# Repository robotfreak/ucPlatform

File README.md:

# ucPlatform
A nodular micro controller test platform. For different micro controller boards(arduino nano, adafruit feather, wio terminal). Support libraries for different controllers (atmega, arm cortex, esp8266, esp32, rp2040) and different . Modular system with test boards for different uses (basisc io, sensors, actors)

# micro controller boards

Each board has a similar design. There is a female header connector for the controller board. 

## IOs

All IOs of the controller boards have 3pin breakout connectors (signal, vcc, gnd). Depending on the controller IO supply voltage the IO pins headers are 3.3V or 5V compatble. For external components that needs 5V on a 3.3V system or 3.3V on a 5V system there is a level shifter for 4 IOs on board  

## Power supply 

An external power supply (6..12V round connector 5.5mm outer 2.1mm inner diameter) is needed. Also an USB cable to power the controller board. The controller board will not be powered from the external power supply and vice versa, the controller board will not power any external components.

On each board is an onboard power supply to generate 5V and 3.3V for the controller and the peripheral. A standarized connector will supply add on boards with 5V, 3.3V and the output voltage of the external power supply.

## Arduino nano board

Board for classic 8bit Arduino controllers like Arduino nano, or micro. 5V compatible IOs, 3V3 support via onboard level converter. The Arduino Nano has 14 digital IOs and 8 analog inputs. Some pins with special functions like:
* UART (Rx, Tx) 
* I2C (sda, scl)
* SPI (miso, mosi, sck, en) 

## Adafruit Feather board

Board for controller boards compatible to Adafruit feather. There exists Adafruit Feather boards for most modern 32bit micro controllers that exists on the market like:
* ARM Cortex M0 or M4, 
* ESP8266 and ESP32, 
* Raspberry Pi RP2040, 
* nRF51 and nRF52  

Most boards has ports with special functions like:
* UART (rx, tx), 
* I2C (sda, scl),
* SPI (miso, mosi, sck, en)
* I2S (digital audio interface)
* DAC (digital analog converter)

## Seeed Studio Wio Terminal / Raspberry Pi board

The Seeed Studio Wio Terminal is a powerful conmtroller board with an ARM Cortex M4 controller, an extra WiFi controller, onboard TFT display, mini joystick and 2 buttons. All IOs are on a 40pins header on the buttom of the board. The pinout is compatible to the Rasperry Pi, so instead of the Wio Terminal a Raspberry Pi can be connected to this board

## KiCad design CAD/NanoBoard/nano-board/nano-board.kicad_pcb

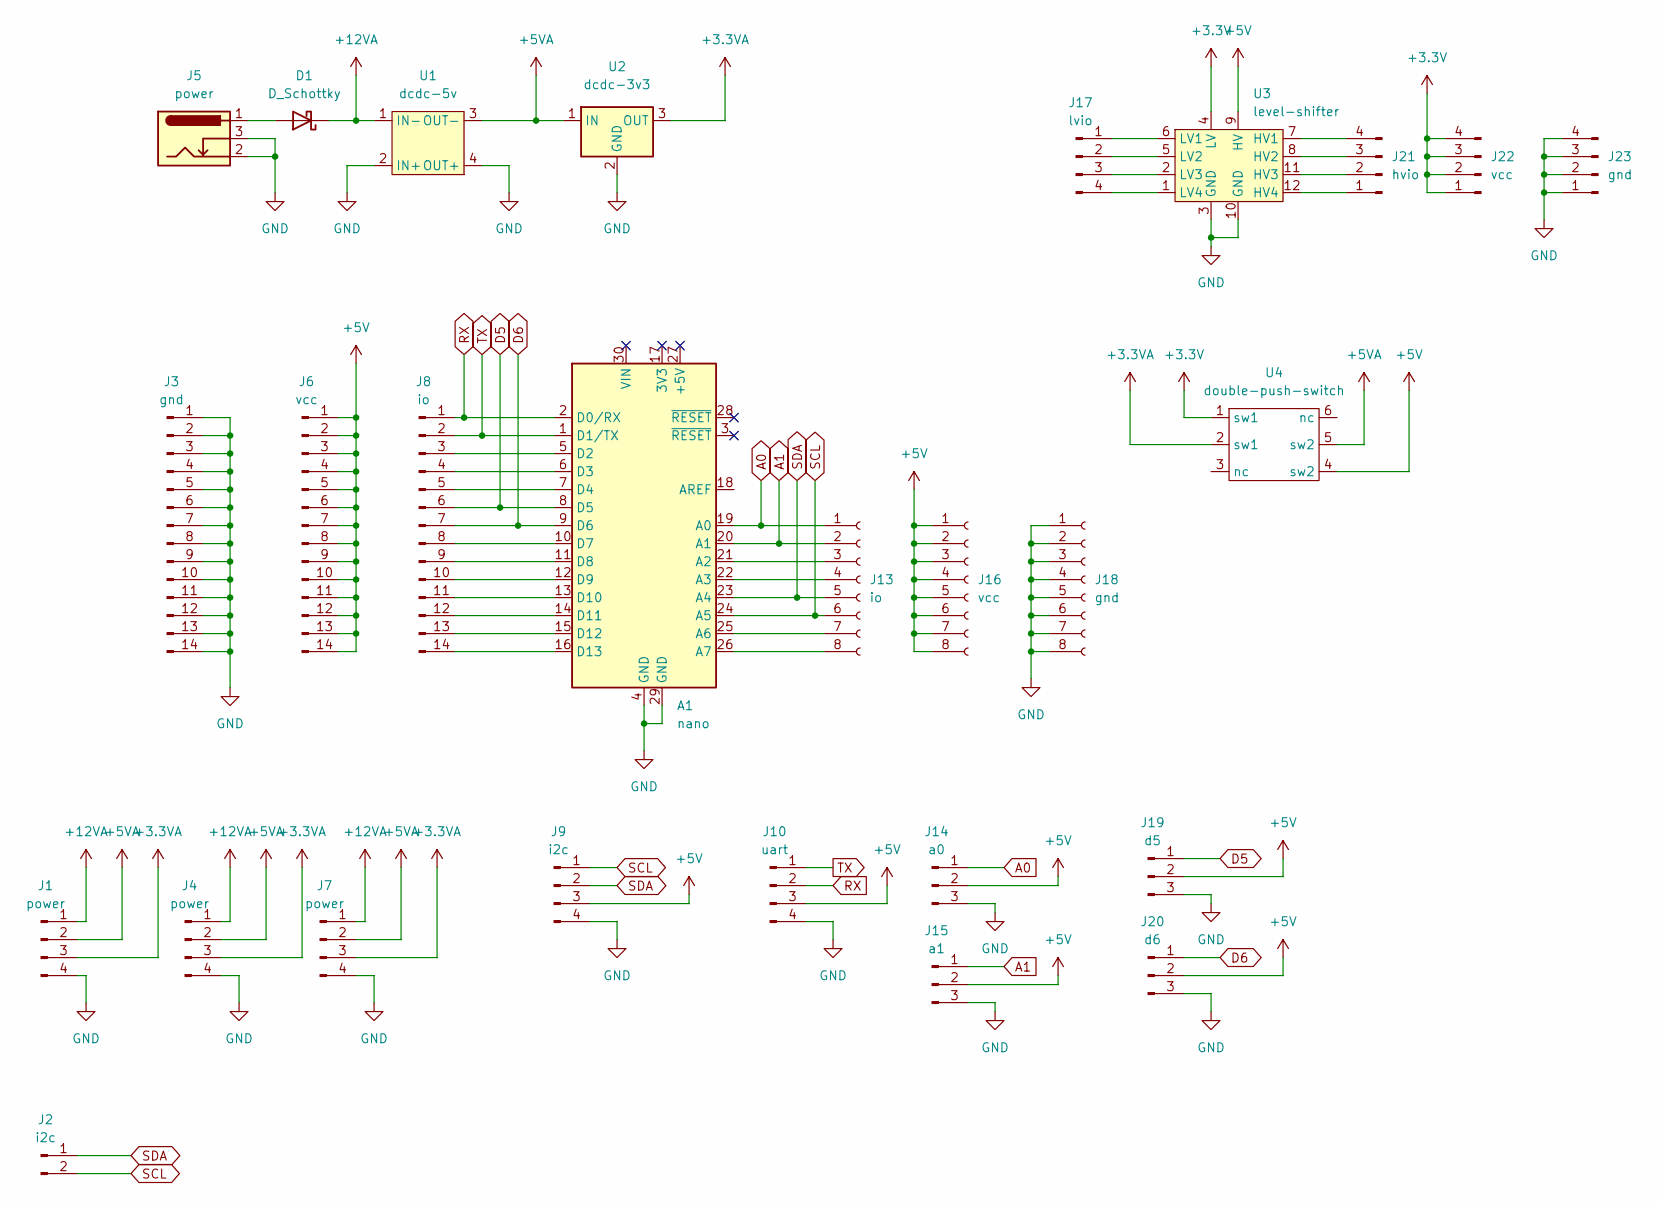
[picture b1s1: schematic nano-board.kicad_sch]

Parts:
A1: nano; Arduino_Nano
D1: D_Schottky; D_1210_3225Metric
J1, J4, J7: power; TerminalBlock_bornier-4_P5.08mm
J2: i2c; TerminalBlock_bornier-2_P5.08mm
J3: gnd; PinSocket_1x14_P2.54mm_Vertical
J5: power; BarrelJack_Horizontal
J6: vcc; PinSocket_1x14_P2.54mm_Vertical
J8: io; PinSocket_1x14_P2.54mm_Vertical
J9: i2c; PinSocket_1x04_P2.54mm_Vertical
J10: uart; PinSocket_1x04_P2.54mm_Vertical
J13: io; PinSocket_1x08_P2.54mm_Vertical
J14: a0; PinSocket_1x03_P2.54mm_Vertical
J15: a1; PinSocket_1x03_P2.54mm_Vertical
J16: vcc; PinSocket_1x08_P2.54mm_Vertical
J17: lvio; PinSocket_1x04_P2.54mm_Vertical
J18: gnd; PinSocket_1x08_P2.54mm_Vertical
J19: d5; PinSocket_1x03_P2.54mm_Vertical
J20: d6; PinSocket_1x03_P2.54mm_Vertical
J21: hvio; PinSocket_1x04_P2.54mm_Vertical
J22: vcc; PinSocket_1x04_P2.54mm_Vertical
J23: gnd; PinSocket_1x04_P2.54mm_Vertical
U1: dcdc-5v; dcdc-converter
U2: dcdc-3v3; Converter_DCDC_Murata_OKI-78SR_Vertical
U3: level-shifter; dip-12pin
U4: double-push-switch; dip-6pin

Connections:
+3.3V: J22.1, J22.2, J22.3, J22.4, U3.4 (LV), U4.1 (sw1)
+3.3VA: J1.3, J4.3, J7.3, U2.3 (OUT), U4.2 (sw1)
+5V: J6.1, J6.2, J6.3, J6.4, J6.5, J6.6, J6.7, J6.8, J6.9, J6.10, J6.11, J6.12, J6.13, J6.14, J9.3, J10.3, J14.2, J15.2, J16.1, J16.2, J16.3, J16.4, J16.5, J16.6, J16.7, J16.8, J19.2, J20.2, U3.9 (HV), U4.4 (sw2)
+5VA: J1.2, J4.2, J7.2, U1.3 (OUT-), U2.1 (IN), U4.5 (sw2)
+12VA: D1.1 (K), J1.1, J4.1, J7.1, U1.1 (IN-)
A0: A1.19 (A0), J13.1, J14.1
A1: A1.20 (A1), J13.2, J15.1
D5: A1.8 (D5), J8.6, J19.1
D6: A1.9 (D6), J8.7, J20.1
GND: A1.4 (GND), A1.29 (GND), J1.4, J3.1, J3.2, J3.3, J3.4, J3.5, J3.6, J3.7, J3.8, J3.9, J3.10, J3.11, J3.12, J3.13, J3.14, J4.4, J5.2, J5.3, J7.4, J9.4, J10.4, J14.3, J15.3, J18.1, J18.2, J18.3, J18.4, J18.5, J18.6, J18.7, J18.8, J19.3, J20.3, J23.1, J23.2, J23.3, J23.4, U1.2 (IN+), U1.4 (OUT+), U2.2 (GND), U3.3 (GND), U3.10 (GND)
unnamed: A1.5 (D2), J8.3
unnamed: A1.6 (D3), J8.4
unnamed: A1.7 (D4), J8.5
unnamed: A1.10 (D7), J8.8
unnamed: A1.11 (D8), J8.9
unnamed: A1.12 (D9), J8.10
unnamed: A1.13 (D10), J8.11
unnamed: A1.14 (D11), J8.12
unnamed: A1.15 (D12), J8.13
unnamed: A1.16 (D13), J8.14
unnamed: A1.21 (A2), J13.3
unnamed: A1.22 (A3), J13.4
unnamed: A1.25 (A6), J13.7
unnamed: A1.26 (A7), J13.8
unnamed: D1.2 (A), J5.1
unnamed: J17.1, U3.6 (LV1)
unnamed: J17.2, U3.5 (LV2)
unnamed: J17.3, U3.2 (LV3)
unnamed: J17.4, U3.1 (LV4)
unnamed: J21.1, U3.12 (HV4)
unnamed: J21.2, U3.11 (HV3)
unnamed: J21.3, U3.8 (HV2)
unnamed: J21.4, U3.7 (HV1)
RX: A1.2 (D0/RX), J8.1, J10.2
SCL: A1.24 (A5), J2.2, J9.1, J13.6
SDA: A1.23 (A4), J2.1, J9.2, J13.5
TX: A1.1 (D1/TX), J8.2, J10.1

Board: 2 copper layers, 27 parts (0 on the bottom side), 37 nets, no tracks yet.

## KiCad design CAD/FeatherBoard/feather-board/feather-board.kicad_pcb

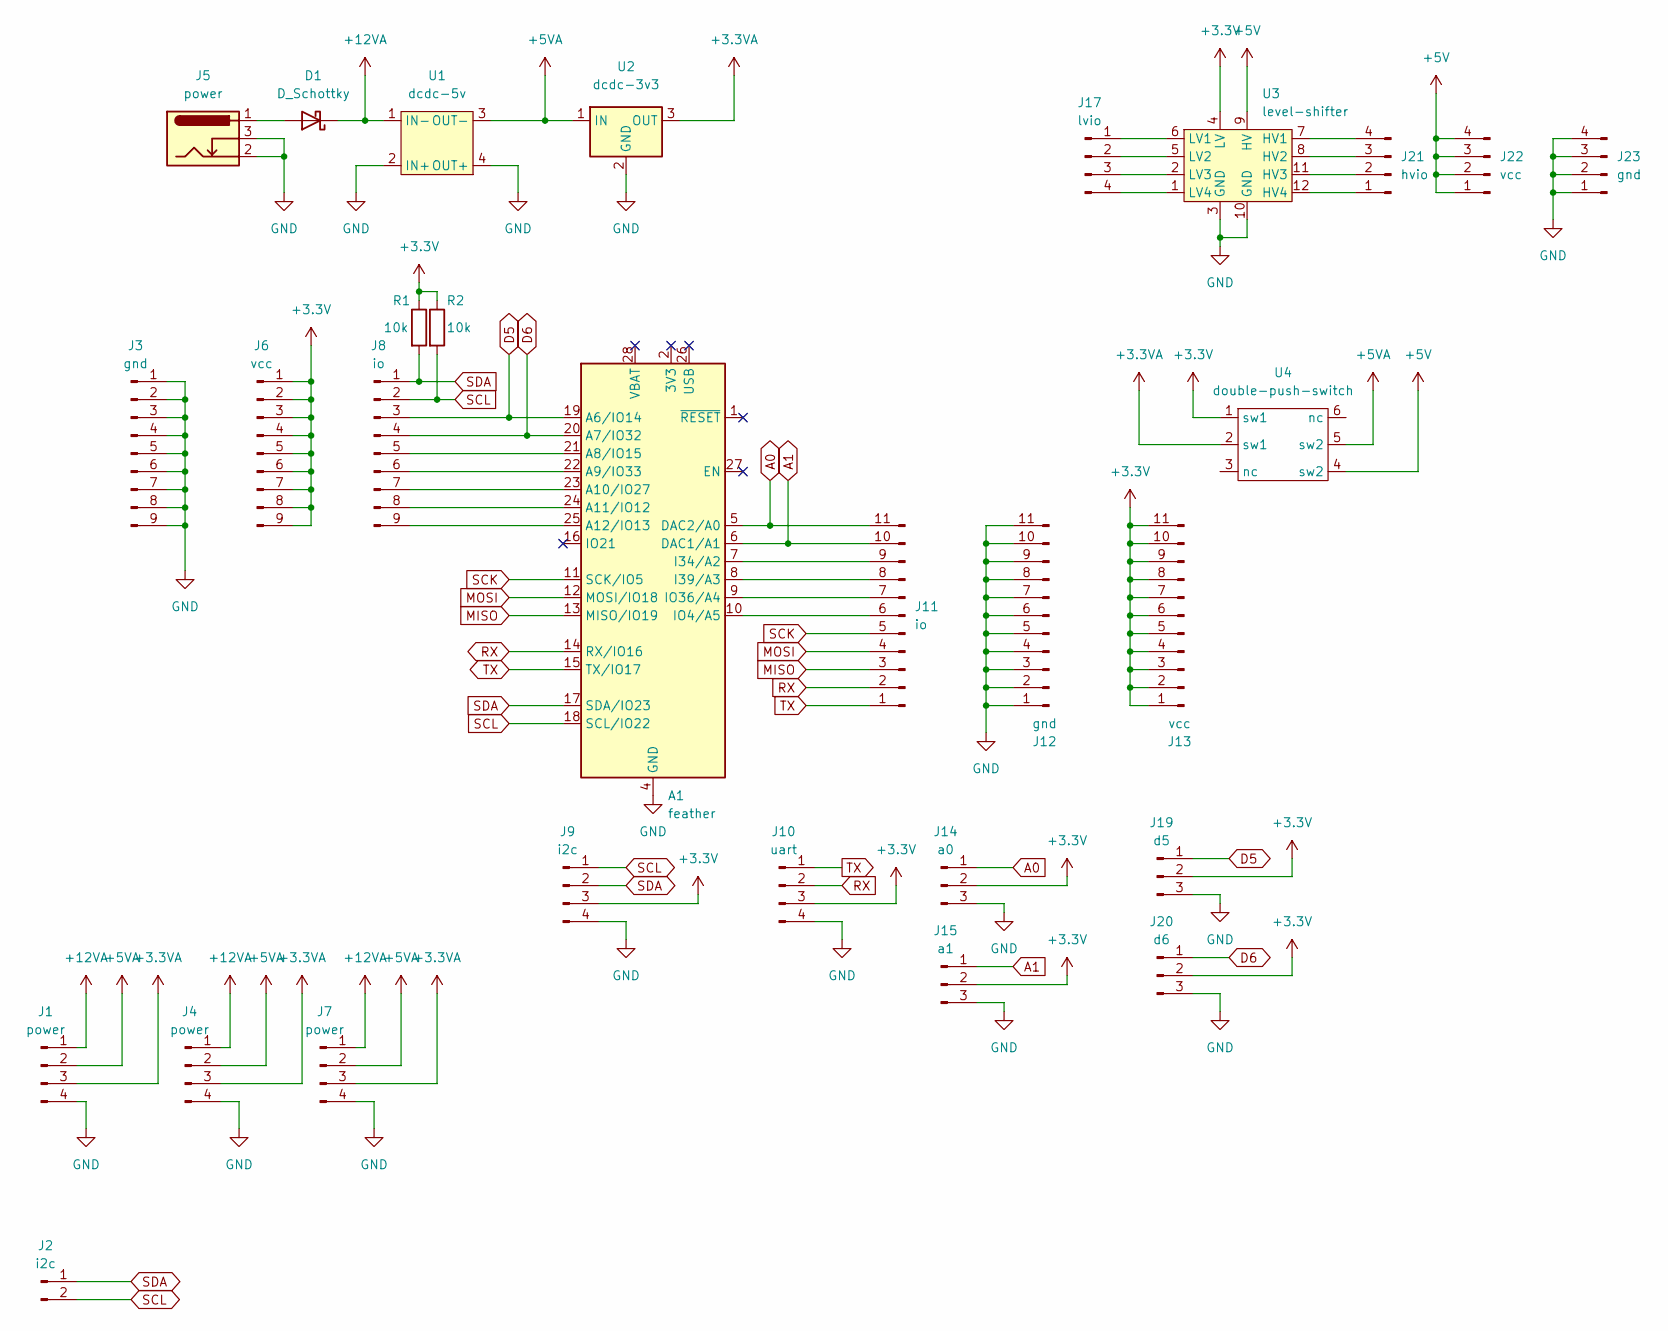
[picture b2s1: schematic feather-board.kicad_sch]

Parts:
A1: feather; Adafruit_Feather
D1: D_Schottky; D_1210_3225Metric
J1, J4, J7: power; TerminalBlock_bornier-4_P5.08mm
J2: i2c; TerminalBlock_bornier-2_P5.08mm
J3: gnd; PinHeader_1x09_P2.54mm_Vertical
J5: power; BarrelJack_Horizontal
J6: vcc; PinHeader_1x09_P2.54mm_Vertical
J8: io; PinHeader_1x09_P2.54mm_Vertical
J9: i2c; PinSocket_1x04_P2.54mm_Vertical
J10: uart; PinSocket_1x04_P2.54mm_Vertical
J11: io; PinHeader_1x11_P2.54mm_Vertical
J12: gnd; PinHeader_1x11_P2.54mm_Vertical
J13: vcc; PinHeader_1x11_P2.54mm_Vertical
J14: a0; PinSocket_1x03_P2.54mm_Vertical
J15: a1; PinSocket_1x03_P2.54mm_Vertical
J17: lvio; PinSocket_1x04_P2.54mm_Vertical
J19: d5; PinSocket_1x03_P2.54mm_Vertical
J20: d6; PinSocket_1x03_P2.54mm_Vertical
J21: hvio; PinSocket_1x04_P2.54mm_Vertical
J22: vcc; PinSocket_1x04_P2.54mm_Vertical
J23: gnd; PinSocket_1x04_P2.54mm_Vertical
R1, R2: 10k; R_1206_3216Metric
U1: dcdc-5v; dcdc-converter
U2: dcdc-3v3; Converter_DCDC_Murata_OKI-78SR_Vertical
U3: level-shifter; dip-12pin
U4: double-push-switch; dip-6pin

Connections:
+3.3V: J6.1, J6.2, J6.3, J6.4, J6.5, J6.6, J6.7, J6.8, J6.9, J9.3, J10.3, J13.1, J13.2, J13.3, J13.4, J13.5, J13.6, J13.7, J13.8, J13.9, J13.10, J13.11, J14.2, J15.2, J19.2, J20.2, R1.1, R2.1, U3.4 (LV), U4.1 (sw1)
+3.3VA: J1.3, J4.3, J7.3, U2.3 (OUT), U4.2 (sw1)
+5V: J22.1, J22.2, J22.3, J22.4, U3.9 (HV), U4.4 (sw2)
+5VA: J1.2, J4.2, J7.2, U1.3 (OUT-), U2.1 (IN), U4.5 (sw2)
+12VA: D1.1 (K), J1.1, J4.1, J7.1, U1.1 (IN-)
A0: A1.5 (DAC2/A0), J11.11, J14.1
A1: A1.6 (DAC1/A1), J11.10, J15.1
D5: A1.19 (A6/IO14), J8.3, J19.1
D6: A1.20 (A7/IO32), J8.4, J20.1
GND: A1.4 (GND), J1.4, J3.1, J3.2, J3.3, J3.4, J3.5, J3.6, J3.7, J3.8, J3.9, J4.4, J5.2, J5.3, J7.4, J9.4, J10.4, J12.1, J12.2, J12.3, J12.4, J12.5, J12.6, J12.7, J12.8, J12.9, J12.10, J12.11, J14.3, J15.3, J19.3, J20.3, J23.1, J23.2, J23.3, J23.4, U1.2 (IN+), U1.4 (OUT+), U2.2 (GND), U3.3 (GND), U3.10 (GND)
MISO: A1.13 (MISO/IO19), J11.3
MOSI: A1.12 (MOSI/IO18), J11.4
unnamed: A1.7 (I34/A2), J11.9
unnamed: A1.8 (I39/A3), J11.8
unnamed: A1.9 (IO36/A4), J11.7
unnamed: A1.10 (IO4/A5), J11.6
unnamed: A1.21 (A8/IO15), J8.5
unnamed: A1.22 (A9/IO33), J8.6
unnamed: A1.23 (A10/IO27), J8.7
unnamed: A1.24 (A11/IO12), J8.8
unnamed: A1.25 (A12/IO13), J8.9
unnamed: D1.2 (A), J5.1
unnamed: J17.1, U3.6 (LV1)
unnamed: J17.2, U3.5 (LV2)
unnamed: J17.3, U3.2 (LV3)
unnamed: J17.4, U3.1 (LV4)
unnamed: J21.1, U3.12 (HV4)
unnamed: J21.2, U3.11 (HV3)
unnamed: J21.3, U3.8 (HV2)
unnamed: J21.4, U3.7 (HV1)
RX: A1.14 (RX/IO16), J10.2, J11.2
SCK: A1.11 (SCK/IO5), J11.5
SCL: A1.18 (SCL/IO22), J2.2, J8.2, J9.1, R2.2
SDA: A1.17 (SDA/IO23), J2.1, J8.1, J9.2, R1.2
TX: A1.15 (TX/IO17), J10.1, J11.1

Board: 2 copper layers, 29 parts (0 on the bottom side), 35 nets, no tracks yet.

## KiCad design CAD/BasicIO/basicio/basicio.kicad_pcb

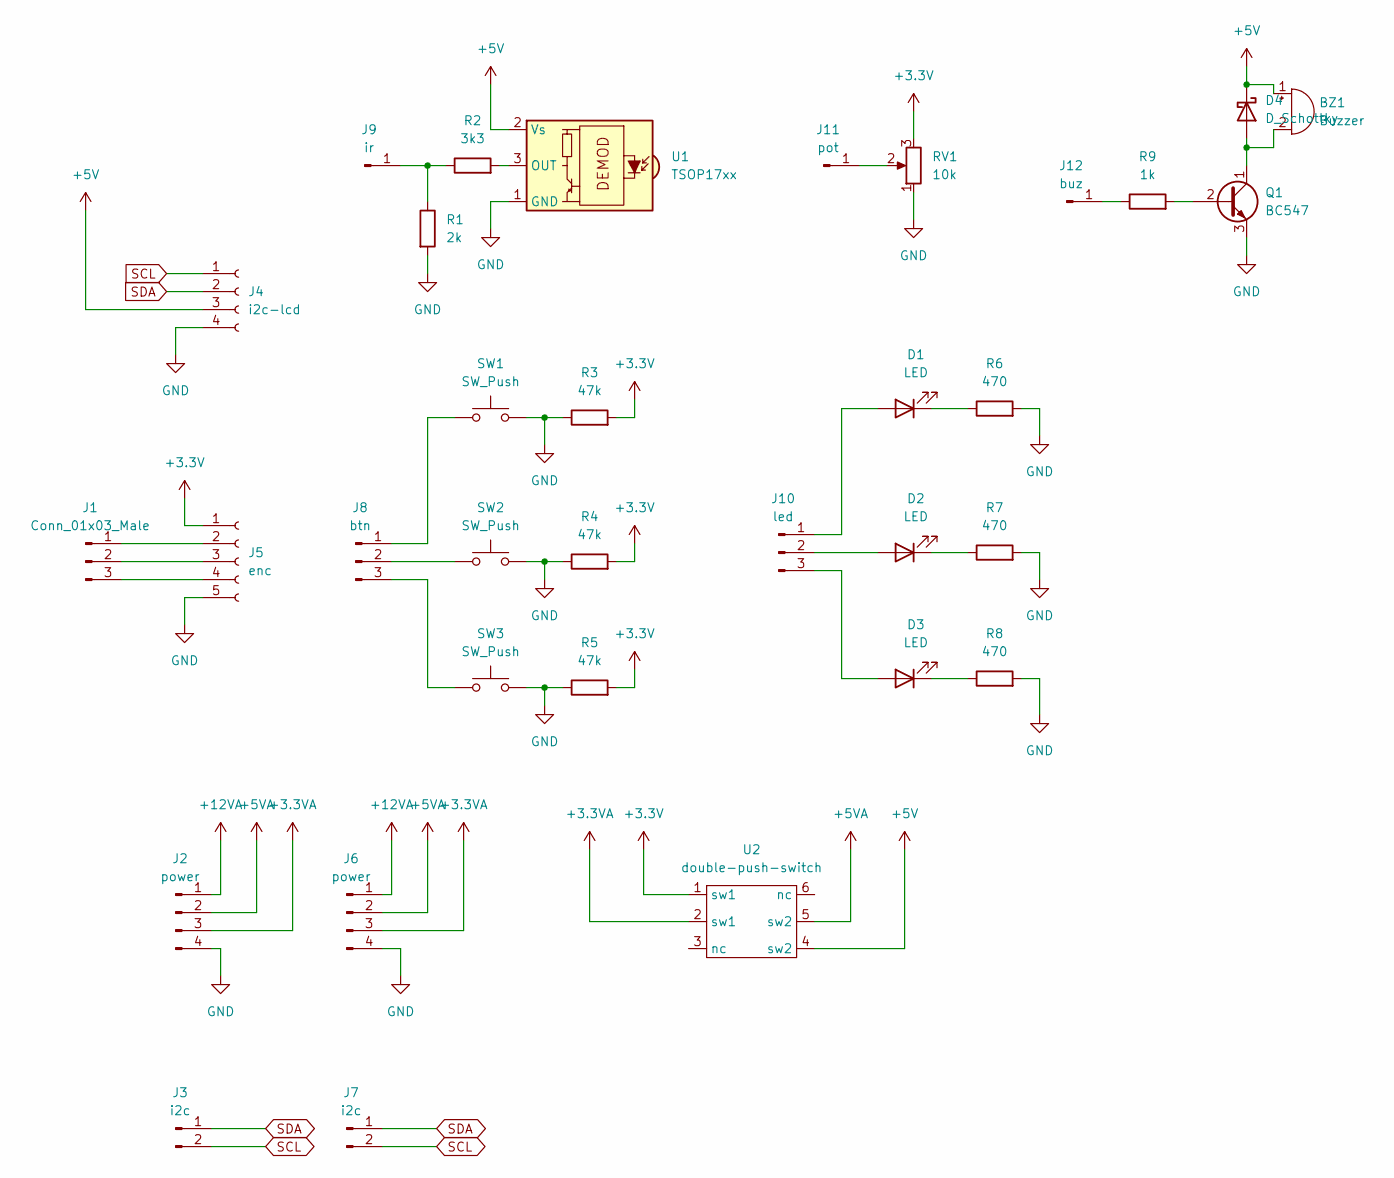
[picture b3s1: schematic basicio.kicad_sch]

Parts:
BZ1: Buzzer; Buzzer_12x9.5RM7.6
D1, D2, D3: LED; LED_D5.0mm
D4: D_Schottky; D_A-405_P7.62mm_Horizontal
J1: Conn_01x03_Male; PinHeader_1x03_P2.54mm_Vertical
J2, J6: power; TerminalBlock_bornier-4_P5.08mm
J3, J7: i2c; TerminalBlock_bornier-2_P5.08mm
J4: i2c-lcd; PinSocket_1x04_P2.54mm_Vertical
J5: enc; PinSocket_1x05_P2.54mm_Vertical
J8: btn; PinHeader_1x03_P2.54mm_Vertical
J9: ir; PinHeader_1x01_P2.54mm_Vertical
J10: led; PinHeader_1x03_P2.54mm_Vertical
J11: pot; PinHeader_1x01_P2.54mm_Vertical
J12: buz; PinHeader_1x01_P2.54mm_Vertical
Q1: BC547; TO-92_Inline
R1: 2k; R_1206_3216Metric
R2: 3k3; R_1206_3216Metric
R3, R4, R5: 47k; R_1206_3216Metric
R6, R7, R8: 470; R_1206_3216Metric
R9: 1k; R_1206_3216Metric
RV1: 10k; Potentiometer_Alps_RK163_Single_Horizontal
SW1, SW2, SW3: SW_Push; SW_PUSH-12mm
U1: TSOP17xx; Vishay_CAST-3Pin
U2: double-push-switch; dip-6pin

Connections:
+3.3V: J5.1, R3.2, R4.2, R5.2, RV1.3, U2.1 (sw1)
+3.3VA: J2.3, J6.3, U2.2 (sw1)
+5V: BZ1.1 (-), D4.1 (K), J4.3, U1.2 (Vs), U2.4 (sw2)
+5VA: J2.2, J6.2, U2.5 (sw2)
+12VA: J2.1, J6.1
GND: J2.4, J4.4, J5.5, J6.4, Q1.3 (E), R1.2, R3.1, R4.1, R5.1, R6.2, R7.2, R8.2, RV1.1, SW1.2, SW2.2, SW3.2, U1.1 (GND)
unnamed: BZ1.2 (+), D4.2 (A), Q1.1 (C)
unnamed: D1.1 (K), R6.1
unnamed: D1.2 (A), J10.1
unnamed: D2.1 (K), R7.1
unnamed: D2.2 (A), J10.2
unnamed: D3.1 (K), R8.1
unnamed: D3.2 (A), J10.3
unnamed: J1.1, J5.2
unnamed: J1.2, J5.3
unnamed: J1.3, J5.4
unnamed: J8.1, SW1.1
unnamed: J8.2, SW2.1
unnamed: J8.3, SW3.1
unnamed: J9.1, R1.1, R2.1
unnamed: J11.1, RV1.2
unnamed: J12.1, R9.1
unnamed: Q1.2 (B), R9.2
unnamed: R2.2, U1.3 (OUT)
SCL: J3.2, J4.1, J7.2
SDA: J3.1, J4.2, J7.1

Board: 2 copper layers, 33 parts (0 on the bottom side), 26 nets, no tracks yet.

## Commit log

2023-04-08 add arduino basicioboard example
2023-04-08 changed liquidcrystal library to LiquidCrystalIO
2023-04-08 code restrucrured
2023-04-08 added encoder
2023-04-09 added tone
2023-04-14 added basioio board
2023-04-14 added feather board
2023-04-14 added nano board
2023-04-14 added feather board mods
2023-04-14 added basicboard arduino example
